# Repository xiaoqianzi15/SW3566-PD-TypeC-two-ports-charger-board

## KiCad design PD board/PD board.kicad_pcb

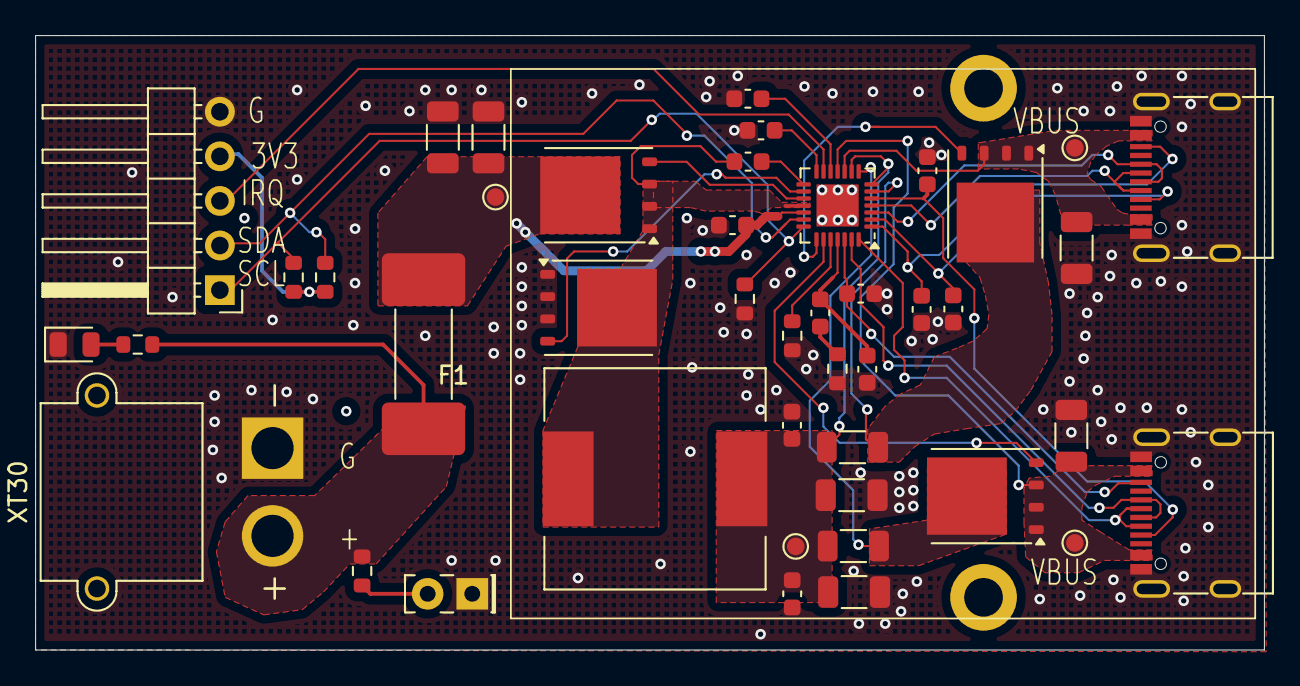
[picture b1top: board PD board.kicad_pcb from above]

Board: 2 copper layers, 70.0 x 35.0 mm, 46 parts (0 on the bottom side), 33 nets.

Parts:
C4, C5, C39, C40: 330pF; C_0603_1608Metric
C6, C17: 10uF; C_1206_3216Metric
C8: 100pF; C_0603_1608Metric
C9: 2.2nF; C_0603_1608Metric
C10, C11: 1uF; C_0603_1608Metric
C12, C13, C15, C16: 0.1uF; C_0603_1608Metric
C14, C41: 22uF; C_1206_3216Metric
C24: 10uF35V; C_1206_3216Metric
C25: 100uF35V; C_1206_3216Metric
F1: Fuse_Small; Fuse_Schurter_UMZ250
H1, H2: MountingHole_Pad; MountingHole_2.2mm_M2_DIN965_Pad
J1, J6: USB_C_Receptacle_USB2.0_16P; USB_C_Receptacle_G-Switch_GT-USB-7010ASV
J3: Conn_01x05_Pin; PinHeader_1x05_P2.54mm_Horizontal
L1: 22uH; L_12x12mm_H8mm
LED1: LED_Small; LED_0805_2012Metric
LED2: LED_Small; LED_Rectangular_W5.0mm_H2.0mm
Q8, Q9, Q10, Q11: CSD17578Q5A; TDSON-8-1
R14, R16: 15K; R_0603_1608Metric
R17, R28: 5mΩ; R_1206_3216Metric
R25: 20K; R_0603_1608Metric
R26: 104AT; R_0603_1608Metric
R27, R38, R39: 68K; R_0603_1608Metric
TP6, TP8, TP9, TP10: TestPoint; TestPoint_Pad_D1.0mm
U2: QFN-28-1EP_4x4mm_P0.4mm_EP2.4x2.4mm
XT30: Conn_01x02; AMASS_XT30PW-M_1x02_P2.50mm_Horizontal

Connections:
+3V3: J3.4, R38.1, R39.1
/CC11: C5.1, J6.A5 (CC1), U2.2 (CC11)
/CC12: C39.1, J1.A5 (CC1), U2.5 (CC12)
/CC21: C4.1, J6.B5 (CC2), U2.1 (CC21)
/CC22: C40.2, J1.B5 (CC2), U2.26 (CC22)
/CSN1: Q10.5 (D), R28.2, U2.6 (CSP1)
/CSN2: Q11.5 (D), R17.2, U2.8 (CSN2)
/CSP: C14.1, C15.1, C16.1, C41.1, L1.2, R17.1, R28.1, TP9.1, U2.7 (CSN1), U2.9 (CSP2)
/DM2: J1.A7 (D-), J1.B7 (D-), U2.28 (DM2)
/DM11: J6.A7 (D-), J6.B7 (D-), U2.4 (DM1)
/DP2: J1.A6 (D+), J1.B6 (D+), U2.27 (DP2)
/DP11: J6.A6 (D+), J6.B6 (D+), U2.3 (DP1)
/GATE1: Q10.4 (G), U2.22 (GATE1)
/GATE2: Q11.4 (G), U2.23 (GATE2)
/IRQ: J3.3, U2.13 (IRQ/ONLINE2)
/SCK: J3.1, R27.2, R38.2, U2.21 (SCK/PSET)
/SDA: J3.2, R39.2, U2.20 (SDA/ONLINE1)
/U1_SW1: C12.1, L1.1, Q8.1 (S), Q8.2 (S), Q8.3 (S), Q9.5 (D), U2.18 (SW)
/VBUS1: C17.1, J6.A4 (VBUS), J6.A9 (VBUS), J6.B4 (VBUS), J6.B9 (VBUS), Q10.1 (S), Q10.2 (S), Q10.3 (S), TP6.1, U2.10 (VBUS1)
/VBUS2: C6.1, J1.A4 (VBUS), J1.A9 (VBUS), J1.B4 (VBUS), J1.B9 (VBUS), Q11.1 (S), Q11.2 (S), Q11.3 (S), TP8.1, U2.11 (VBUS2)
/VDD: C10.1, U2.12 (VDD)
BAT12V: C13.1, C24.1, C25.1, F1.1, Q8.5 (D), TP10.1, U2.19 (VIN)
GND: C4.2, C5.2, C6.2, C8.1, C10.2, C11.2, C13.2, C14.2, C15.2, C16.2, C17.2, C24.2, C25.2, C39.2, C40.1, C41.2, J1.A1 (GND), J1.A12 (GND), J1.B1 (GND), J1.B12 (GND), J1.S1 (SHIELD), J3.5, J6.A1 (GND), J6.A12 (GND), J6.B1 (GND), J6.B12 (GND), J6.S1 (SHIELD), LED1.1 (K), LED2.1 (K), Q9.1 (S), Q9.2 (S), Q9.3 (S), R25.1, R26.1, R27.1, XT30.1
unnamed: C9.1, R25.2
unnamed: LED1.2 (A), R14.2
unnamed: LED2.2 (A), R16.2
unnamed: Q8.4 (G), U2.17 (HGATE)
unnamed: Q9.4 (G), U2.16 (LGATE)
unnamed: C12.2, U2.15 (BST)
unnamed: C8.2, C9.2, U2.25 (COMP)
unnamed: R26.2, U2.24 (NTC)
unnamed: C11.1, U2.14 (VDRV)
unnamed: F1.2, R14.1, R16.1, XT30.2
